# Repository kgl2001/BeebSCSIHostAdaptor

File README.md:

# BeebSCSIHostAdaptor
SCSI Host Adaptor that allows BBC &amp; Master Computers to interface with various SCSI Hard Disk Drives.

Please refer to the following discussion on Stardot for further details: https://stardot.org.uk/forums/viewtopic.php?f=3&t=18815

## Author

BeebSCSIHostAdaptor is developed and maintained by Ken Lowe.

The design is based on the BeebSCSI project by Simon Inns: https://github.com/simoninns/BeebSCSI

## Software License (GPLv3)

    BeebSCSI is free software: you can redistribute it and/or modify
    it under the terms of the GNU General Public License as published by
    the Free Software Foundation, either version 3 of the License, or
    (at your option) any later version.

    BeebSCSI is distributed in the hope that it will be useful,
    but WITHOUT ANY WARRANTY; without even the implied warranty of
    MERCHANTABILITY or FITNESS FOR A PARTICULAR PURPOSE.  See the
    GNU General Public License for more details.

    You should have received a copy of the GNU General Public License
    along with BeebSCSI.  If not, see <http://www.gnu.org/licenses/>.
    
## Hardware License (Creative Commons BY-SA 4.0)

Please see the following link for details: https://creativecommons.org/licenses/by-sa/4.0/

You are free to:

Share - copy and redistribute the material in any medium or format
Adapt - remix, transform, and build upon the material
for any purpose, even commercially.

This license is acceptable for Free Cultural Works.

The licensor cannot revoke these freedoms as long as you follow the license terms.

Under the following terms:

Attribution - You must give appropriate credit, provide a link to the license, and indicate if changes were made. You may do so in any reasonable manner, but not in any way that suggests the licensor endorses you or your use.

ShareAlike - If you remix, transform, or build upon the material, you must distribute your contributions under the same license as the original.

No additional restrictions - You may not apply legal terms or technological measures that legally restrict others from doing anything the license permits.

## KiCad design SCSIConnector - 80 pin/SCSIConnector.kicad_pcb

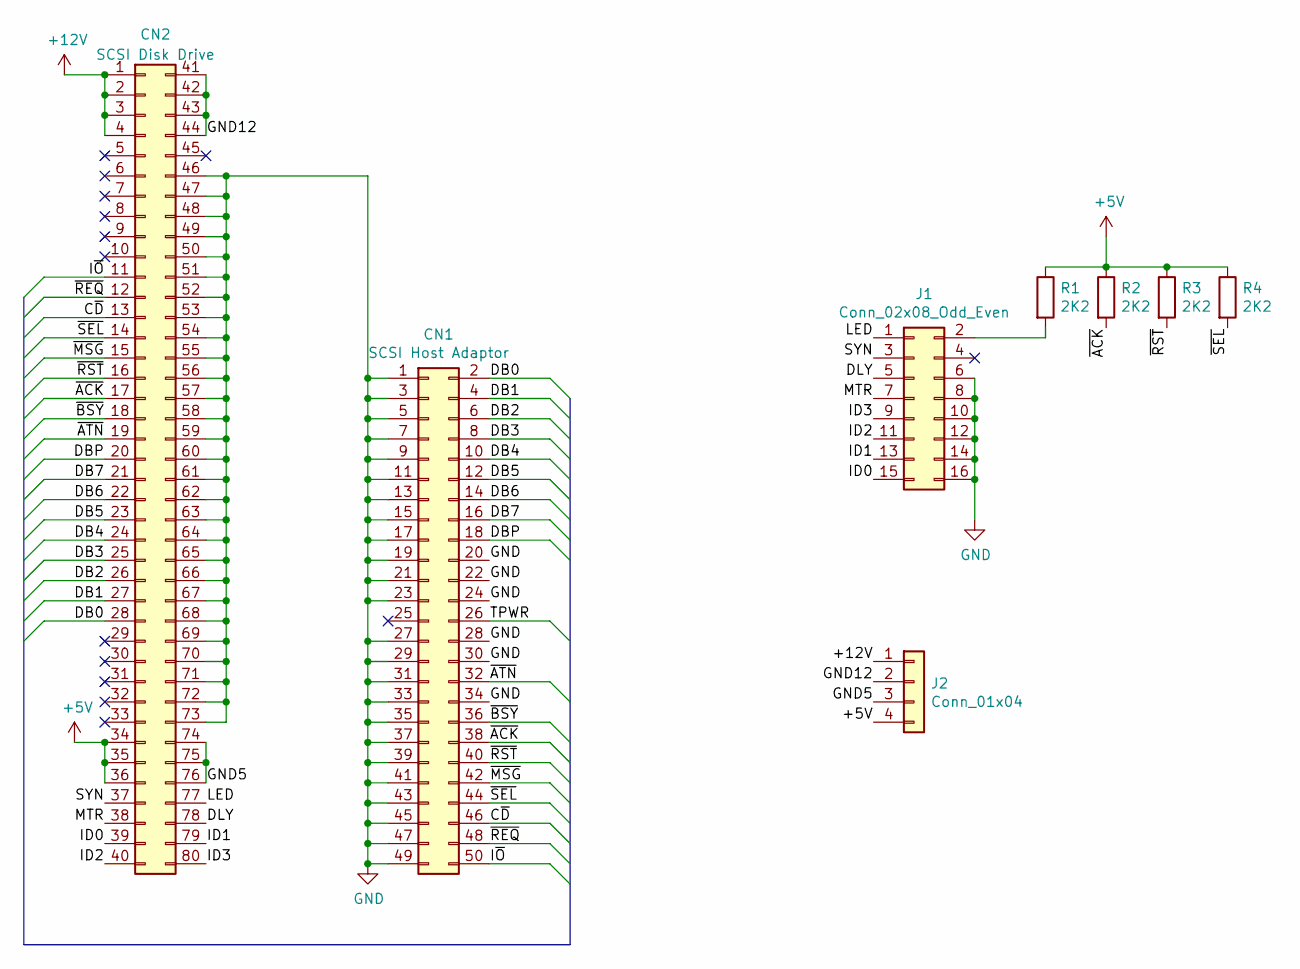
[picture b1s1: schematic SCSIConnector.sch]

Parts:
CN1: SCSI Host Adaptor; PinSocket_2x25_P2.54mm_Vertical
CN2: SCSI Disk Drive; TE_787311-4
J1: Conn_02x08_Odd_Even; PinHeader_2x08_P2.54mm_Vertical
J2: Conn_01x04; conn_hdd_15-24-4449
R1, R2, R3, R4: 2K2; R_Axial_DIN0204_L3.6mm_D1.6mm_P5.08mm_Horizontal

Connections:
+5V: CN2.34, CN2.35, CN2.36, J2.4, R1.1, R2.1, R3.1, R4.1
+12V: CN2.1, CN2.2, CN2.3, CN2.4, J2.1
/C~D: CN1.46, CN2.13
/DB0: CN1.2, CN2.28
/DB1: CN1.4, CN2.27
/DB2: CN1.6, CN2.26
/DB3: CN1.8, CN2.25
/DB4: CN1.10, CN2.24
/DB5: CN1.12, CN2.23
/DB6: CN1.14, CN2.22
/DB7: CN1.16, CN2.21
/DBP: CN1.18, CN2.20
/DLY: CN2.78, J1.5
/GND5: CN2.74, CN2.75, CN2.76, J2.3
/GND12: CN2.41, CN2.42, CN2.43, CN2.44, J2.2
/ID0: CN2.39, J1.15
/ID1: CN2.79, J1.13
/ID2: CN2.40, J1.11
/ID3: CN2.80, J1.9
/I~O: CN1.50, CN2.11
/LED: CN2.77, J1.1
/MTR: CN2.38, J1.7
/SYN: CN2.37, J1.3
/TPWR: CN1.26
/~ACK: CN1.38, CN2.17, R2.2
/~ATN: CN1.32, CN2.19
/~BSY: CN1.36, CN2.18
/~MSG: CN1.42, CN2.15
/~REQ: CN1.48, CN2.12
/~RST: CN1.40, CN2.16, R3.2
/~SEL: CN1.44, CN2.14, R4.2
GND: CN1.1, CN1.3, CN1.5, CN1.7, CN1.9, CN1.11, CN1.13, CN1.15, CN1.17, CN1.19, CN1.20, CN1.21, CN1.22, CN1.23, CN1.24, CN1.27, CN1.28, CN1.29, CN1.30, CN1.31, CN1.33, CN1.34, CN1.35, CN1.37, CN1.39, CN1.41, CN1.43, CN1.45, CN1.47, CN1.49, CN2.46, CN2.47, CN2.48, CN2.49, CN2.50, CN2.51, CN2.52, CN2.53, CN2.54, CN2.55, CN2.56, CN2.57, CN2.58, CN2.59, CN2.60, CN2.61, CN2.62, CN2.63, CN2.64, CN2.65, CN2.66, CN2.67, CN2.68, CN2.69, CN2.70, CN2.71, CN2.72, CN2.73, J1.6, J1.8, J1.10, J1.12, J1.14, J1.16
unnamed: J1.2, R1.2

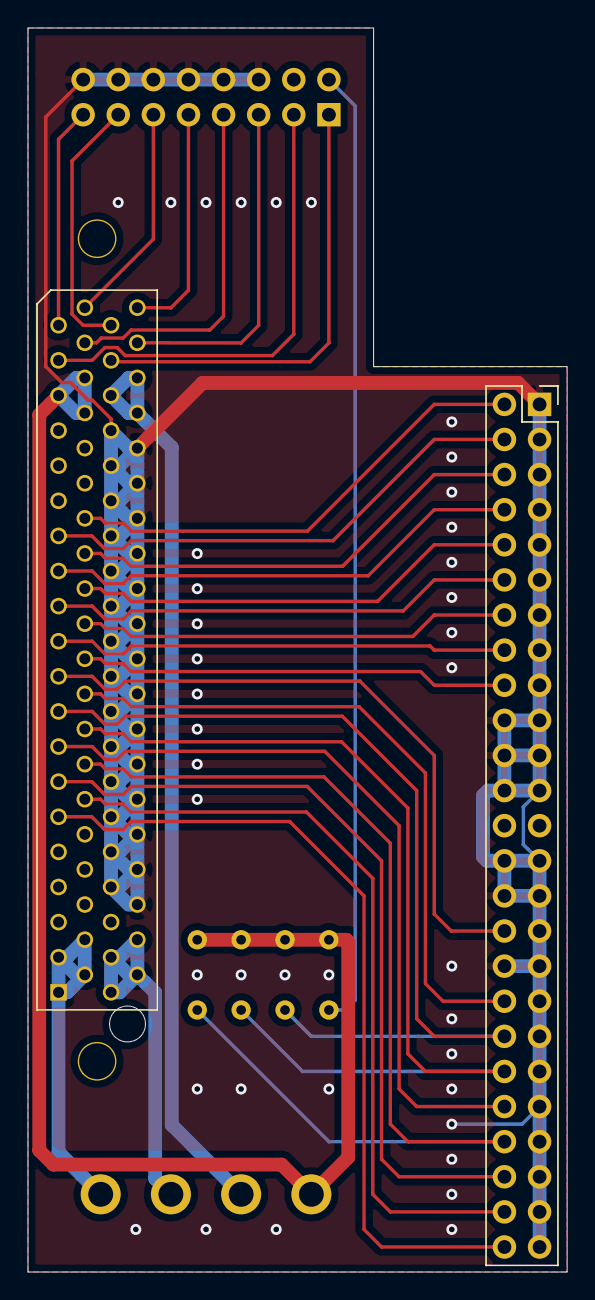
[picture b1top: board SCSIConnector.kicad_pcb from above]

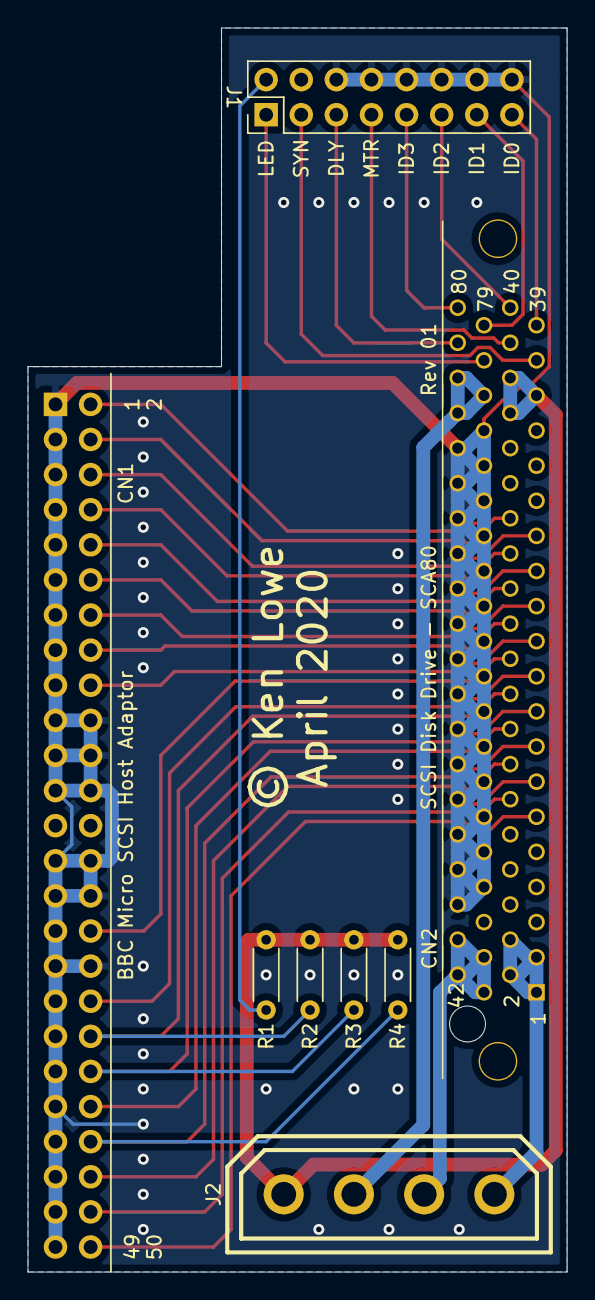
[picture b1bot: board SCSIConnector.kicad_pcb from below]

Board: 2 copper layers, 39.0 x 90.0 mm, 8 parts (6 on the bottom side), 32 nets.

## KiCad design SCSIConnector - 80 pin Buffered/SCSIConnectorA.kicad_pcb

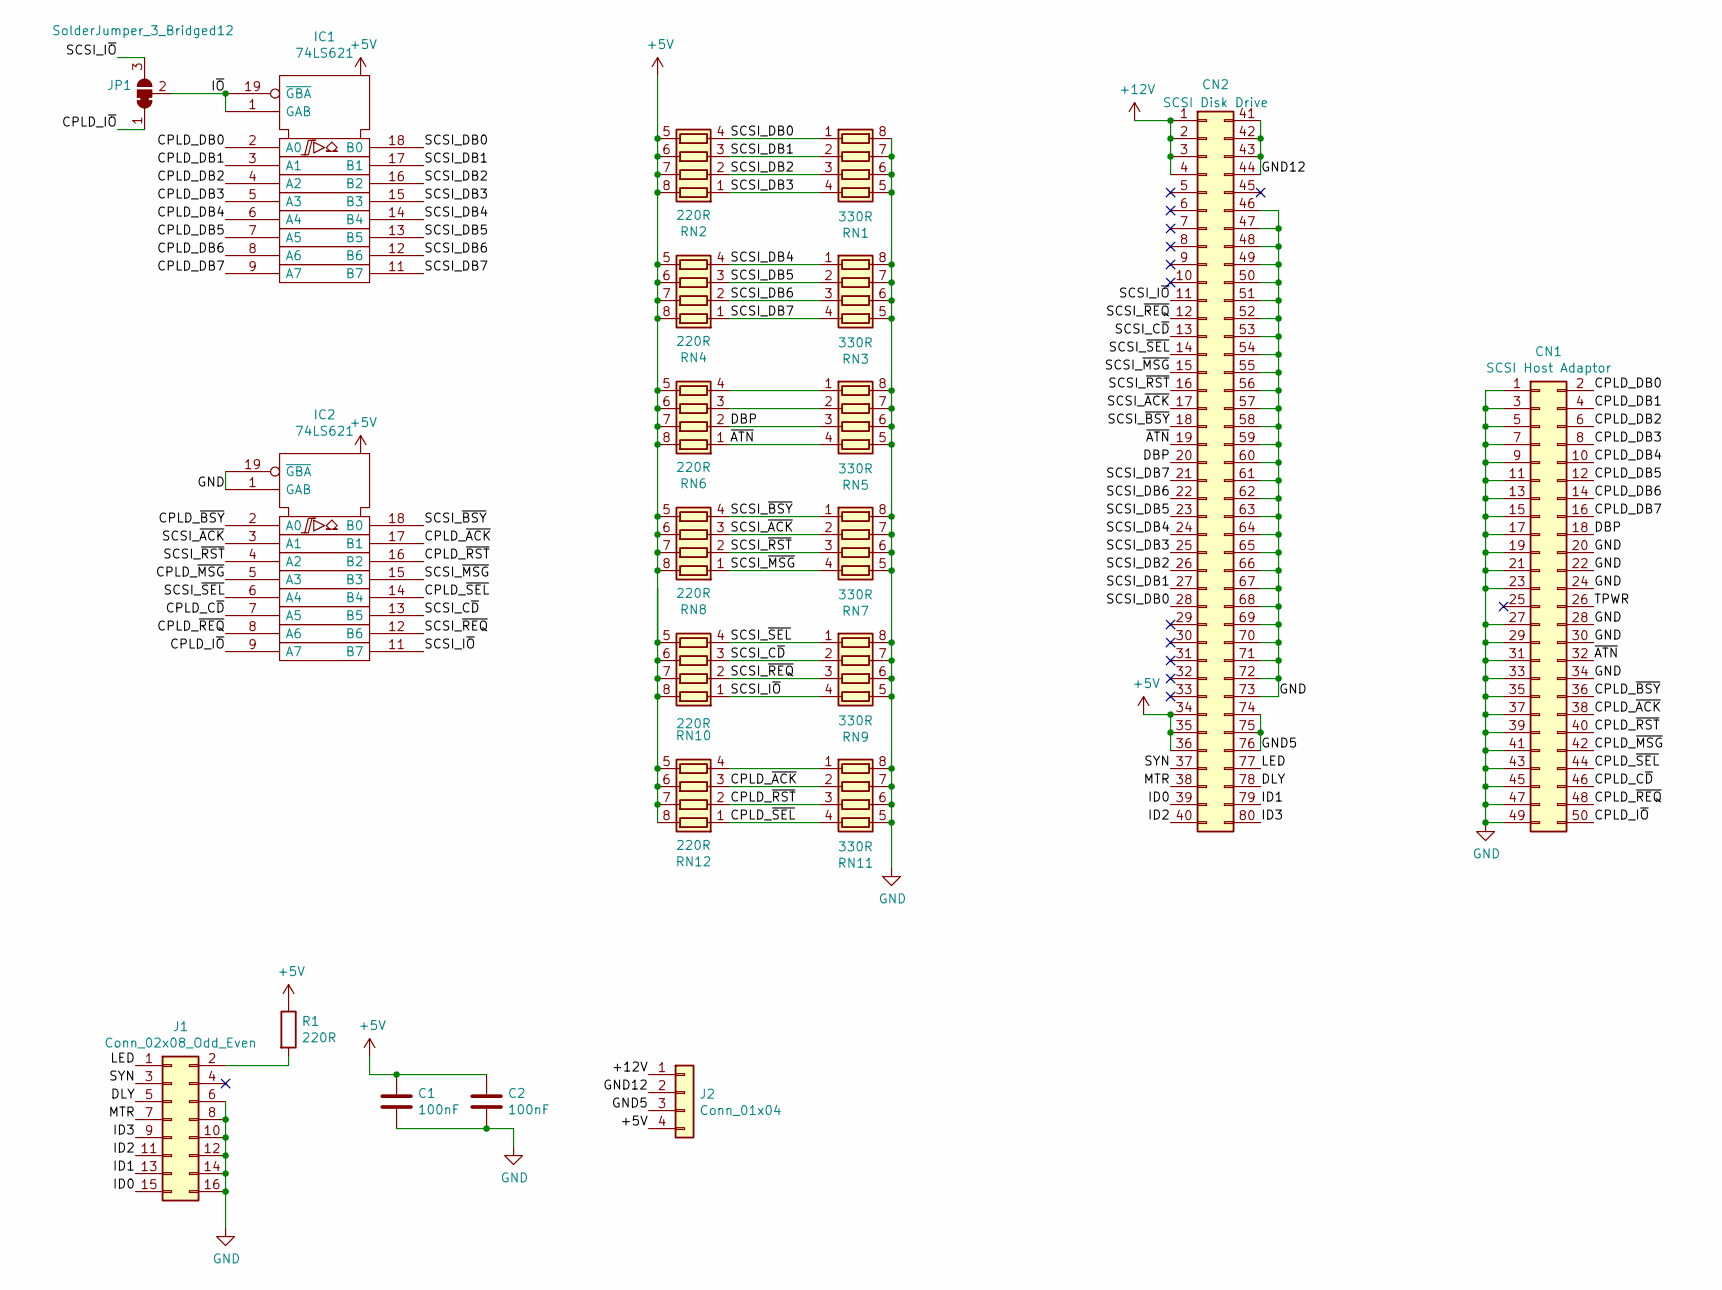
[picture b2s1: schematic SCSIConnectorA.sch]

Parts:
C1, C2: 100nF; C_0603_1608Metric
CN1: SCSI Host Adaptor; PinSocket_2x25_P2.54mm_Vertical
CN2: SCSI Disk Drive; TE_787311-4
IC1, IC2: 74LS621; SOIC-20W_7.5x12.8mm_P1.27mm
J1: Conn_02x08_Odd_Even; PinHeader_2x08_P2.54mm_Vertical
J2: Conn_01x04; conn_hdd_15-24-4449
JP1: SolderJumper_3_Bridged12; SolderJumper-3_P1.3mm_Bridged12_RoundedPad1.0x1.5mm
R1: 220R; R_0603_1608Metric
RN1, RN3, RN5, RN7, RN9, RN11: 330R; R_Array_Concave_4x0402
RN2, RN4, RN6, RN8, RN10, RN12: 220R; R_Array_Concave_4x0402

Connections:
+5V: C1.1, C2.1, CN2.34, CN2.35, CN2.36, IC1.20 (VCC), IC2.20 (VCC), J2.4, R1.1, RN2.5 (R4.2), RN2.6 (R3.2), RN2.7 (R2.2), RN2.8 (R1.2), RN4.5 (R4.2), RN4.6 (R3.2), RN4.7 (R2.2), RN4.8 (R1.2), RN6.5 (R4.2), RN6.6 (R3.2), RN6.7 (R2.2), RN6.8 (R1.2), RN8.5 (R4.2), RN8.6 (R3.2), RN8.7 (R2.2), RN8.8 (R1.2), RN10.5 (R4.2), RN10.6 (R3.2), RN10.7 (R2.2), RN10.8 (R1.2), RN12.5 (R4.2), RN12.6 (R3.2), RN12.7 (R2.2), RN12.8 (R1.2)
+12V: CN2.1, CN2.2, CN2.3, CN2.4, J2.1
/CPLD_C~D: CN1.46, IC2.7 (A5)
/CPLD_DB0: CN1.2, IC1.2 (A0)
/CPLD_DB1: CN1.4, IC1.3 (A1)
/CPLD_DB2: CN1.6, IC1.4 (A2)
/CPLD_DB3: CN1.8, IC1.5 (A3)
/CPLD_DB4: CN1.10, IC1.6 (A4)
/CPLD_DB5: CN1.12, IC1.7 (A5)
/CPLD_DB6: CN1.14, IC1.8 (A6)
/CPLD_DB7: CN1.16, IC1.9 (A7)
/CPLD_I~O: CN1.50, IC2.9 (A7), JP1.1 (A)
/CPLD_~ACK: CN1.38, IC2.17 (B1), RN11.2 (R2.1), RN12.3 (R3.1)
/CPLD_~BSY: CN1.36, IC2.2 (A0)
/CPLD_~MSG: CN1.42, IC2.5 (A3)
/CPLD_~REQ: CN1.48, IC2.8 (A6)
/CPLD_~RST: CN1.40, IC2.16 (B2), RN11.3 (R3.1), RN12.2 (R2.1)
/CPLD_~SEL: CN1.44, IC2.14 (B4), RN11.4 (R4.1), RN12.1 (R1.1)
/DBP: CN1.18, CN2.20, RN5.3 (R3.1), RN6.2 (R2.1)
/DLY: CN2.78, J1.5
/GND5: CN2.74, CN2.75, CN2.76, J2.3
/GND12: CN2.41, CN2.42, CN2.43, CN2.44, J2.2
/ID0: CN2.39, J1.15
/ID1: CN2.79, J1.13
/ID2: CN2.40, J1.11
/ID3: CN2.80, J1.9
/I~O: IC1.1 (GAB), IC1.19 (~GBA), JP1.2 (C)
/LED: CN2.77, J1.1
/MTR: CN2.38, J1.7
/SCSI_C~D: CN2.13, IC2.13 (B5), RN9.2 (R2.1), RN10.3 (R3.1)
/SCSI_DB0: CN2.28, IC1.18 (B0), RN1.1 (R1.1), RN2.4 (R4.1)
/SCSI_DB1: CN2.27, IC1.17 (B1), RN1.2 (R2.1), RN2.3 (R3.1)
/SCSI_DB2: CN2.26, IC1.16 (B2), RN1.3 (R3.1), RN2.2 (R2.1)
/SCSI_DB3: CN2.25, IC1.15 (B3), RN1.4 (R4.1), RN2.1 (R1.1)
/SCSI_DB4: CN2.24, IC1.14 (B4), RN3.1 (R1.1), RN4.4 (R4.1)
/SCSI_DB5: CN2.23, IC1.13 (B5), RN3.2 (R2.1), RN4.3 (R3.1)
/SCSI_DB6: CN2.22, IC1.12 (B6), RN3.3 (R3.1), RN4.2 (R2.1)
/SCSI_DB7: CN2.21, IC1.11 (B7), RN3.4 (R4.1), RN4.1 (R1.1)
/SCSI_I~O: CN2.11, IC2.11 (B7), JP1.3 (B), RN9.4 (R4.1), RN10.1 (R1.1)
/SCSI_~ACK: CN2.17, IC2.3 (A1), RN7.2 (R2.1), RN8.3 (R3.1)
/SCSI_~BSY: CN2.18, IC2.18 (B0), RN7.1 (R1.1), RN8.4 (R4.1)
/SCSI_~MSG: CN2.15, IC2.15 (B3), RN7.4 (R4.1), RN8.1 (R1.1)
/SCSI_~REQ: CN2.12, IC2.12 (B6), RN9.3 (R3.1), RN10.2 (R2.1)
/SCSI_~RST: CN2.16, IC2.4 (A2), RN7.3 (R3.1), RN8.2 (R2.1)
/SCSI_~SEL: CN2.14, IC2.6 (A4), RN9.1 (R1.1), RN10.4 (R4.1)
/SYN: CN2.37, J1.3
/TPWR: CN1.26
/~ATN: CN1.32, CN2.19, RN5.4 (R4.1), RN6.1 (R1.1)
GND: C1.2, C2.2, CN1.1, CN1.3, CN1.5, CN1.7, CN1.9, CN1.11, CN1.13, CN1.15, CN1.17, CN1.19, CN1.20, CN1.21, CN1.22, CN1.23, CN1.24, CN1.27, CN1.28, CN1.29, CN1.30, CN1.31, CN1.33, CN1.34, CN1.35, CN1.37, CN1.39, CN1.41, CN1.43, CN1.45, CN1.47, CN1.49, CN2.46, CN2.47, CN2.48, CN2.49, CN2.50, CN2.51, CN2.52, CN2.53, CN2.54, CN2.55, CN2.56, CN2.57, CN2.58, CN2.59, CN2.60, CN2.61, CN2.62, CN2.63, CN2.64, CN2.65, CN2.66, CN2.67, CN2.68, CN2.69, CN2.70, CN2.71, CN2.72, CN2.73, IC1.10 (GND), IC2.1 (GAB), IC2.10 (GND), IC2.19 (~GBA), J1.6, J1.8, J1.10, J1.12, J1.14, J1.16, RN1.5 (R4.2), RN1.6 (R3.2), RN1.7 (R2.2), RN1.8 (R1.2), RN3.5 (R4.2), RN3.6 (R3.2), RN3.7 (R2.2), RN3.8 (R1.2), RN5.5 (R4.2), RN5.6 (R3.2), RN5.7 (R2.2), RN5.8 (R1.2), RN7.5 (R4.2), RN7.6 (R3.2), RN7.7 (R2.2), RN7.8 (R1.2), RN9.5 (R4.2), RN9.6 (R3.2), RN9.7 (R2.2), RN9.8 (R1.2), RN11.5 (R4.2), RN11.6 (R3.2), RN11.7 (R2.2), RN11.8 (R1.2)
unnamed: J1.2, R1.2
unnamed: RN5.1 (R1.1), RN6.4 (R4.1)
unnamed: RN5.2 (R2.1), RN6.3 (R3.1)
unnamed: RN11.1 (R1.1), RN12.4 (R4.1)

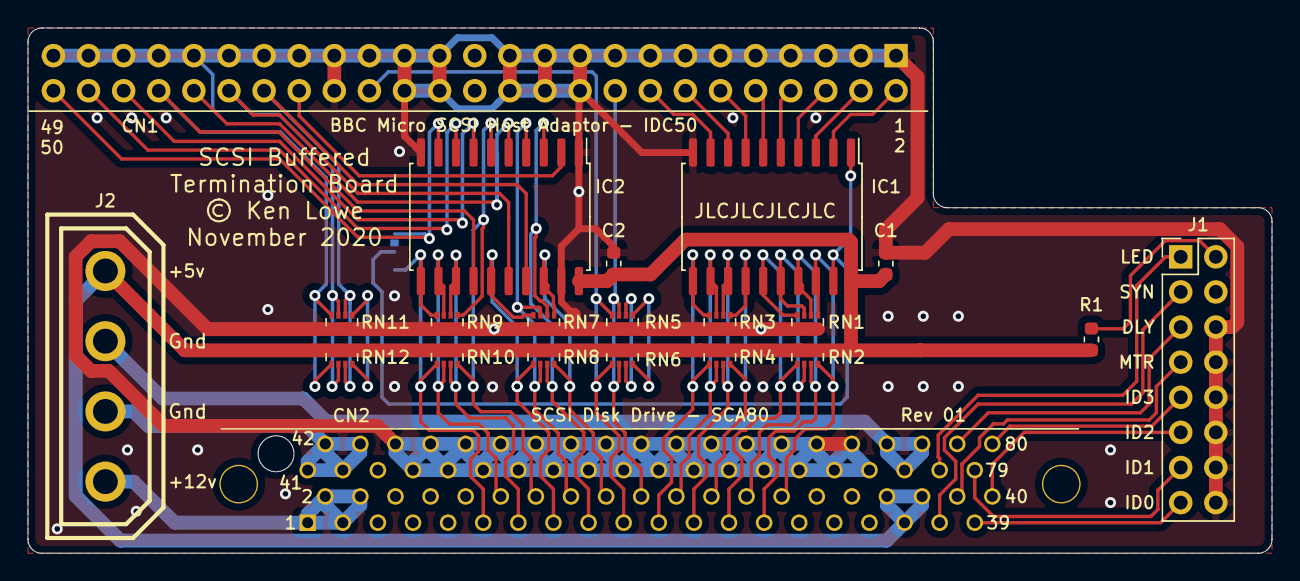
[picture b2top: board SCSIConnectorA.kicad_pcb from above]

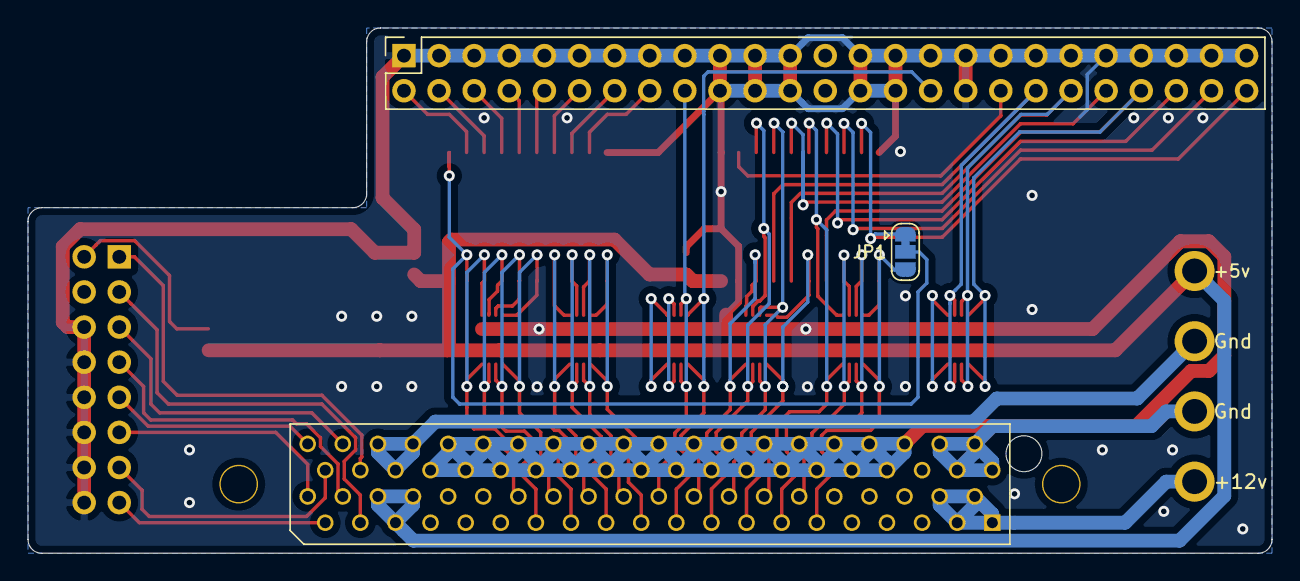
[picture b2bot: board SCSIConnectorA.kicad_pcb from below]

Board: 2 copper layers, 90.0 x 38.0 mm, 22 parts (3 on the bottom side), 52 nets.

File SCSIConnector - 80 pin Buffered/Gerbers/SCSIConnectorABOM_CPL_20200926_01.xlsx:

Designator | LCSC Part # | Footprint | JLCValue | Mid X | Mid Y | Rot | Side | Val | Package
C1 | C14663 | 0603 | 100nF | 156.83000000000001 | -74.819999999999993 | 90 | top | 100uF | C_0603_1608Metric
C2 | C14663 | 0603 | 100nF | 137.14500000000001 | -74.819999999999993 | 90 | top | 100uF | C_0603_1608Metric
IC1 |  |  |  | 148.595 | -71.435000000000002 | 270 | top | 74LS621 | SOIC-20W_7.5x12.8mm_P1.27mm
IC2 |  |  |  | 128.91 | -71.435000000000002 | 270 | top | 74LS621 | SOIC-20W_7.5x12.8mm_P1.27mm
R1 | C22962 | 0603 | 220R | 171.70424 | -80.305080000000004 | 90 | top | 220R | R_0603_1608Metric
RN1 | C102635 | 0402_x4 | 330R | 151.17500000000001 | -79.055000000000007 | 270 | top | 330R | R_Array_Concave_4x0402
RN2 | C25498 | 0402_x4 | 220R | 151.17500000000001 | -81.594999999999999 | 90 | top | 220R | R_Array_Concave_4x0402
RN3 | C102635 | 0402_x4 | 330R | 144.82499999999999 | -79.055000000000007 | 270 | top | 330R | R_Array_Concave_4x0402
RN4 | C25498 | 0402_x4 | 220R | 144.82499999999999 | -81.594999999999999 | 90 | top | 220R | R_Array_Concave_4x0402
RN5 | C102635 | 0402_x4 | 330R | 137.78 | -79.055000000000007 | 270 | top | 330R | R_Array_Concave_4x0402
RN6 | C25498 | 0402_x4 | 220R | 137.78 | -81.594999999999999 | 90 | top | 220R | R_Array_Concave_4x0402
RN7 | C102635 | 0402_x4 | 330R | 132.08500000000001 | -79.055000000000007 | 270 | top | 330R | R_Array_Concave_4x0402
RN8 | C25498 | 0402_x4 | 220R | 132.08500000000001 | -81.594999999999999 | 90 | top | 220R | R_Array_Concave_4x0402
RN9 | C102635 | 0402_x4 | 330R | 125.1 | -79.055000000000007 | 270 | top | 330R | R_Array_Concave_4x0402
RN10 | C25498 | 0402_x4 | 220R | 125.1 | -81.594999999999999 | 90 | top | 220R | R_Array_Concave_4x0402
RN11 | C102635 | 0402_x4 | 330R | 117.48 | -79.055000000000007 | 270 | top | 330R | R_Array_Concave_4x0402
RN12 | C25498 | 0402_x4 | 220R | 117.48 | -81.594999999999999 | 90 | top | 220R | R_Array_Concave_4x0402

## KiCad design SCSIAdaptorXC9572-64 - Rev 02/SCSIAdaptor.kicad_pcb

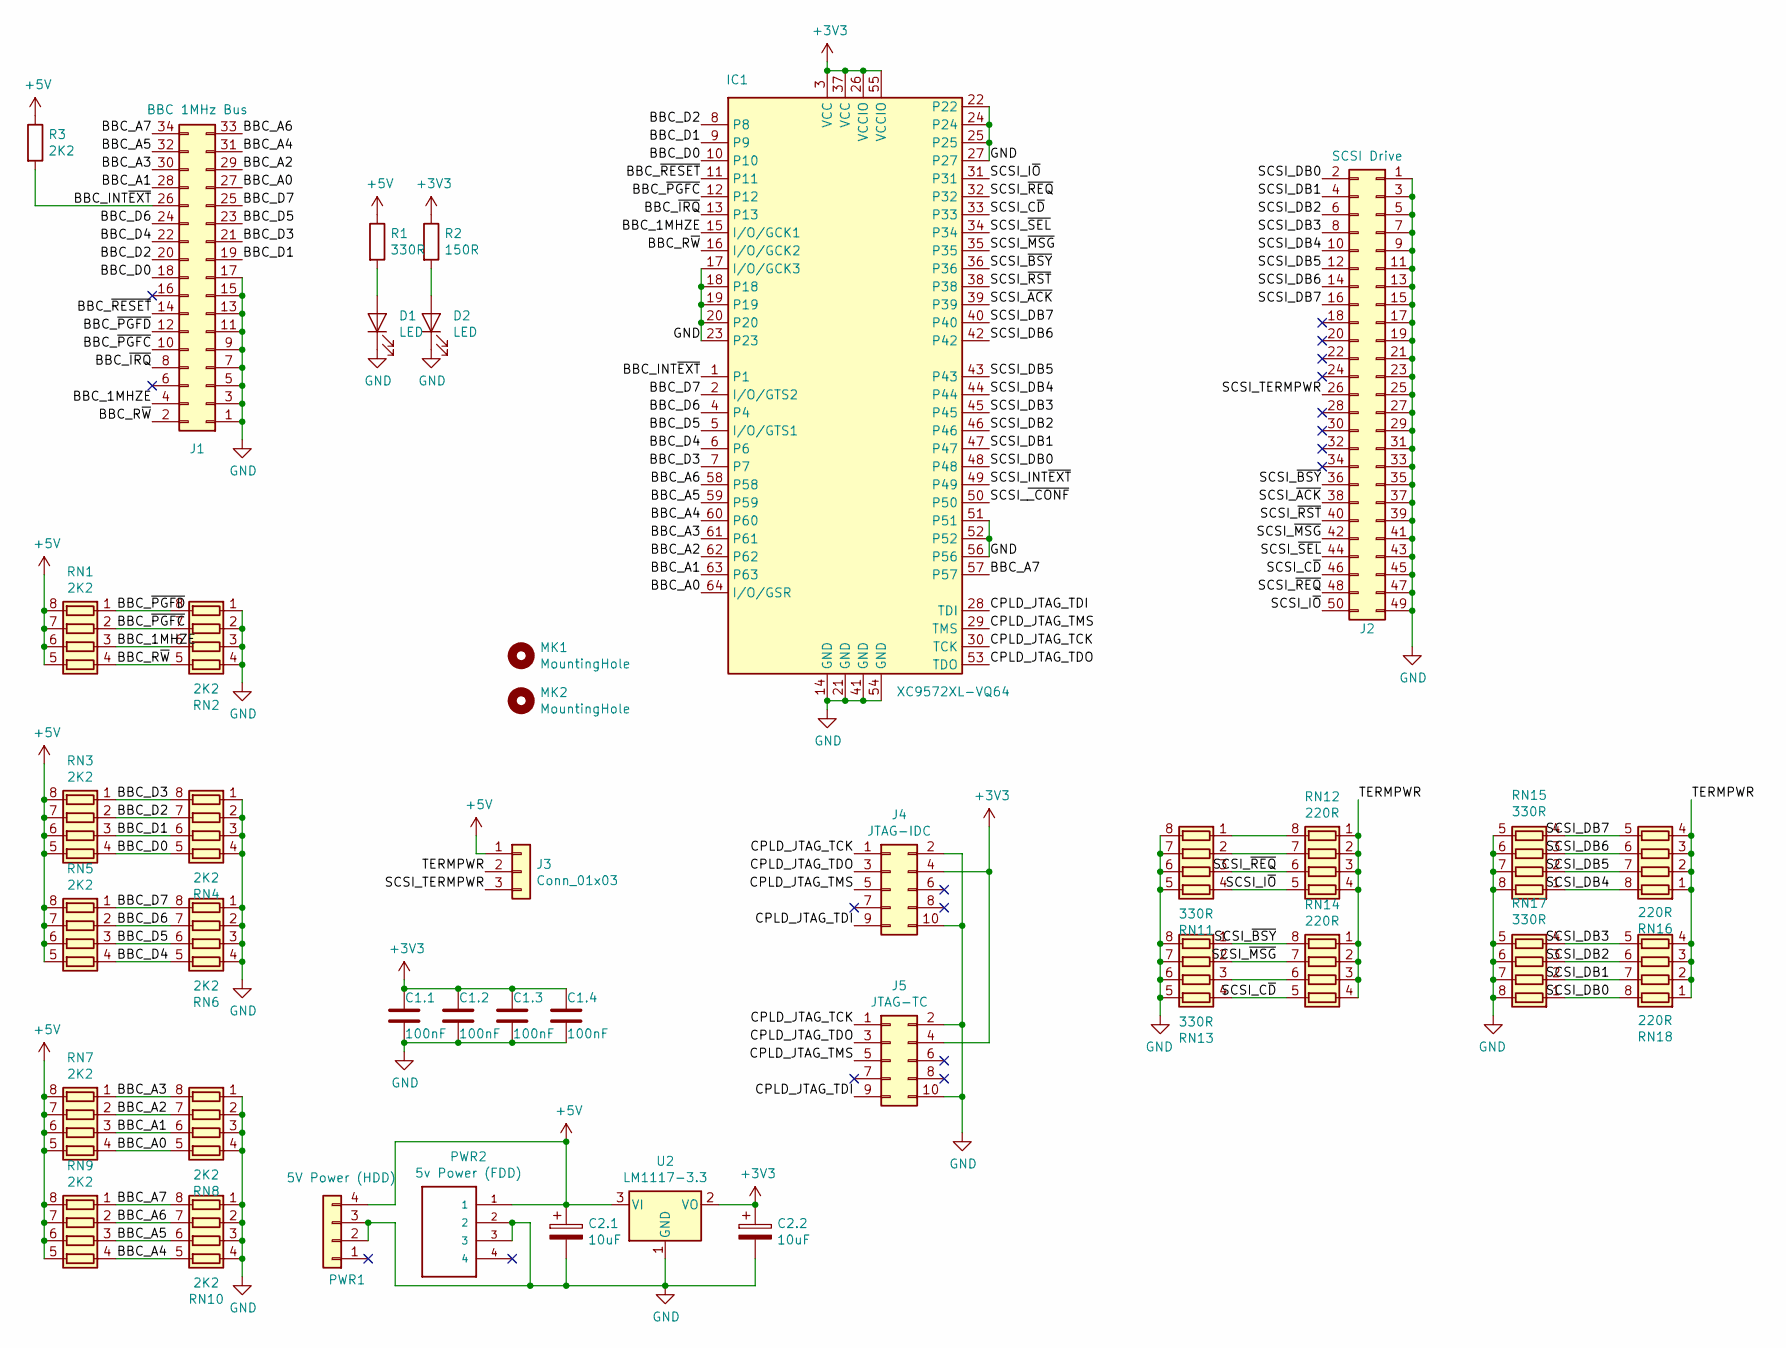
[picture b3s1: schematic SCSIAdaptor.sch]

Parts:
C1.1, C1.2, C1.3, C1.4: 100nF; C_0805_2012Metric
C2.1, C2.2: 10uF; C_1206_3216Metric
D1, D2: LED; LED_0603_1608Metric
IC1: XC9572XL-VQ64; TQFP-64_10x10mm_P0.5mm
J1: BBC 1MHz Bus; IDC-Header_2x17_P2.54mm_Horizontal
J2: SCSI Drive; IDC-Header_2x25_P2.54mm_Horizontal
J3: Conn_01x03; SolderJumper-3_P1.3mm_Bridged12_RoundedPad1.0x1.5mm
J4: JTAG-IDC; PinHeader_2x05_P2.54mm_Vertical
J5: JTAG-TC; Tag-Connect_TC2050-IDC-NL_2x05_P1.27mm_Vertical
MK1, MK2: MountingHole; MountingHole_3.2mm_M3
PWR1: 5V Power (HDD); conn_hdd_15-24-4441
PWR2: 5v Power (FDD); TE_171826-4
R1: 330R; R_0402_1005Metric
R2: 150R; R_0402_1005Metric
R3: 2K2; R_0402_1005Metric
RN1, RN2, RN3, RN4, RN5, RN6, RN7, RN8, RN9, RN10: 2K2; R_Array_Concave_4x0402
RN11, RN13, RN15, RN17: 330R; R_Array_Concave_4x0402
RN12, RN14, RN16, RN18: 220R; R_Array_Concave_4x0402
U2: LM1117-3.3; SOT-223-3_TabPin2

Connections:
+3V3: C1.1.1, C1.2.1, C1.3.1, C1.4.1, C2.2.1, IC1.3 (VCC), IC1.26 (VCCIO), IC1.37 (VCC), IC1.55 (VCCIO), J4.4, J5.4, R2.1, U2.2 (VO)
+5V: C2.1.1, J3.1, PWR1.4, PWR2.1, R1.1, R3.1, RN1.5 (R4.2), RN1.6 (R3.2), RN1.7 (R2.2), RN1.8 (R1.2), RN3.5 (R4.2), RN3.6 (R3.2), RN3.7 (R2.2), RN3.8 (R1.2), RN5.5 (R4.2), RN5.6 (R3.2), RN5.7 (R2.2), RN5.8 (R1.2), RN7.5 (R4.2), RN7.6 (R3.2), RN7.7 (R2.2), RN7.8 (R1.2), RN9.5 (R4.2), RN9.6 (R3.2), RN9.7 (R2.2), RN9.8 (R1.2), U2.3 (VI)
/BBC_1MHZE: IC1.15 (I/O/GCK1), J1.4, RN1.3 (R3.1), RN2.6 (R3.2)
/BBC_A0: IC1.64 (I/O/GSR), J1.27, RN7.4 (R4.1), RN8.5 (R4.2)
/BBC_A1: IC1.63, J1.28, RN7.3 (R3.1), RN8.6 (R3.2)
/BBC_A2: IC1.62, J1.29, RN7.2 (R2.1), RN8.7 (R2.2)
/BBC_A3: IC1.61, J1.30, RN7.1 (R1.1), RN8.8 (R1.2)
/BBC_A4: IC1.60, J1.31, RN9.4 (R4.1), RN10.5 (R4.2)
/BBC_A5: IC1.59, J1.32, RN9.3 (R3.1), RN10.6 (R3.2)
/BBC_A6: IC1.58, J1.33, RN9.2 (R2.1), RN10.7 (R2.2)
/BBC_A7: IC1.57, J1.34, RN9.1 (R1.1), RN10.8 (R1.2)
/BBC_D0: IC1.10, J1.18, RN3.4 (R4.1), RN4.5 (R4.2)
/BBC_D1: IC1.9, J1.19, RN3.3 (R3.1), RN4.6 (R3.2)
/BBC_D2: IC1.8, J1.20, RN3.2 (R2.1), RN4.7 (R2.2)
/BBC_D3: IC1.7, J1.21, RN3.1 (R1.1), RN4.8 (R1.2)
/BBC_D4: IC1.6, J1.22, RN5.4 (R4.1), RN6.5 (R4.2)
/BBC_D5: IC1.5 (I/O/GTS1), J1.23, RN5.3 (R3.1), RN6.6 (R3.2)
/BBC_D6: IC1.4, J1.24, RN5.2 (R2.1), RN6.7 (R2.2)
/BBC_D7: IC1.2 (I/O/GTS2), J1.25, RN5.1 (R1.1), RN6.8 (R1.2)
/BBC_INT~EXT: IC1.1, J1.26, R3.2
/BBC_R~W: IC1.16 (I/O/GCK2), J1.2, RN1.4 (R4.1), RN2.5 (R4.2)
/BBC_~IRQ: IC1.13, J1.8
/BBC_~PGFC: IC1.12, J1.10, RN1.2 (R2.1), RN2.7 (R2.2)
/BBC_~PGFD: J1.12, RN1.1 (R1.1), RN2.8 (R1.2)
/BBC_~RESET: IC1.11, J1.14
/CPLD_JTAG_TCK: IC1.30 (TCK), J4.1, J5.1
/CPLD_JTAG_TDI: IC1.28 (TDI), J4.9, J5.9
/CPLD_JTAG_TDO: IC1.53 (TDO), J4.3, J5.3
/CPLD_JTAG_TMS: IC1.29 (TMS), J4.5, J5.5
/SCSI_C~D: IC1.33, J2.46, RN13.4 (R4.1), RN14.5 (R4.2)
/SCSI_DB0: IC1.48, J2.2, RN17.1 (R1.1), RN18.8 (R1.2)
/SCSI_DB1: IC1.47, J2.4, RN17.2 (R2.1), RN18.7 (R2.2)
/SCSI_DB2: IC1.46, J2.6, RN17.3 (R3.1), RN18.6 (R3.2)
/SCSI_DB3: IC1.45, J2.8, RN17.4 (R4.1), RN18.5 (R4.2)
/SCSI_DB4: IC1.44, J2.10, RN15.1 (R1.1), RN16.8 (R1.2)
/SCSI_DB5: IC1.43, J2.12, RN15.2 (R2.1), RN16.7 (R2.2)
/SCSI_DB6: IC1.42, J2.14, RN15.3 (R3.1), RN16.6 (R3.2)
/SCSI_DB7: IC1.40, J2.16, RN15.4 (R4.1), RN16.5 (R4.2)
/SCSI_INT~EXT: IC1.49
/SCSI_I~O: IC1.31, J2.50, RN11.4 (R4.1), RN12.5 (R4.2)
/SCSI_TERMPWR: J2.26, J3.3
/SCSI_~ACK: IC1.39, J2.38
/SCSI_~BSY: IC1.36, J2.36, RN13.1 (R1.1), RN14.8 (R1.2)
/SCSI_~MSG: IC1.35, J2.42, RN13.2 (R2.1), RN14.7 (R2.2)
/SCSI_~REQ: IC1.32, J2.48, RN11.3 (R3.1), RN12.6 (R3.2)
/SCSI_~RST: IC1.38, J2.40
/SCSI_~SEL: IC1.34, J2.44
/SCSI_~_CONF: IC1.50
/TERMPWR: J3.2, RN12.1 (R1.1), RN12.2 (R2.1), RN12.3 (R3.1), RN12.4 (R4.1), RN14.1 (R1.1), RN14.2 (R2.1), RN14.3 (R3.1), RN14.4 (R4.1), RN16.1 (R1.1), RN16.2 (R2.1), RN16.3 (R3.1), RN16.4 (R4.1), RN18.1 (R1.1), RN18.2 (R2.1), RN18.3 (R3.1), RN18.4 (R4.1)
GND: C1.1.2, C1.2.2, C1.3.2, C1.4.2, C2.1.2, C2.2.2, D1.1 (K), D2.1 (K), IC1.14 (GND), IC1.17 (I/O/GCK3), IC1.18, IC1.19, IC1.20, IC1.21 (GND), IC1.22, IC1.23, IC1.24, IC1.25, IC1.27, IC1.41 (GND), IC1.51, IC1.52, IC1.54 (GND), IC1.56, J1.1, J1.3, J1.5, J1.7, J1.9, J1.11, J1.13, J1.15, J1.17, J2.1, J2.3, J2.5, J2.7, J2.9, J2.11, J2.13, J2.15, J2.17, J2.19, J2.21, J2.23, J2.25, J2.27, J2.29, J2.31, J2.33, J2.35, J2.37, J2.39, J2.41, J2.43, J2.45, J2.47, J2.49, J4.2, J4.10, J5.2, J5.10, PWR1.2, PWR1.3, PWR2.2, PWR2.3, RN2.1 (R1.1), RN2.2 (R2.1), RN2.3 (R3.1), RN2.4 (R4.1), RN4.1 (R1.1), RN4.2 (R2.1), RN4.3 (R3.1), RN4.4 (R4.1), RN6.1 (R1.1), RN6.2 (R2.1), RN6.3 (R3.1), RN6.4 (R4.1), RN8.1 (R1.1), RN8.2 (R2.1), RN8.3 (R3.1), RN8.4 (R4.1), RN10.1 (R1.1), RN10.2 (R2.1), RN10.3 (R3.1), RN10.4 (R4.1), RN11.5 (R4.2), RN11.6 (R3.2), RN11.7 (R2.2), RN11.8 (R1.2), RN13.5 (R4.2), RN13.6 (R3.2), RN13.7 (R2.2), RN13.8 (R1.2), RN15.5 (R4.2), RN15.6 (R3.2), RN15.7 (R2.2), RN15.8 (R1.2), RN17.5 (R4.2), RN17.6 (R3.2), RN17.7 (R2.2), RN17.8 (R1.2), U2.1 (GND)
unnamed: D1.2 (A), R1.2
unnamed: D2.2 (A), R2.2
unnamed: RN11.1 (R1.1), RN12.8 (R1.2)
unnamed: RN11.2 (R2.1), RN12.7 (R2.2)
unnamed: RN13.3 (R3.1), RN14.6 (R3.2)

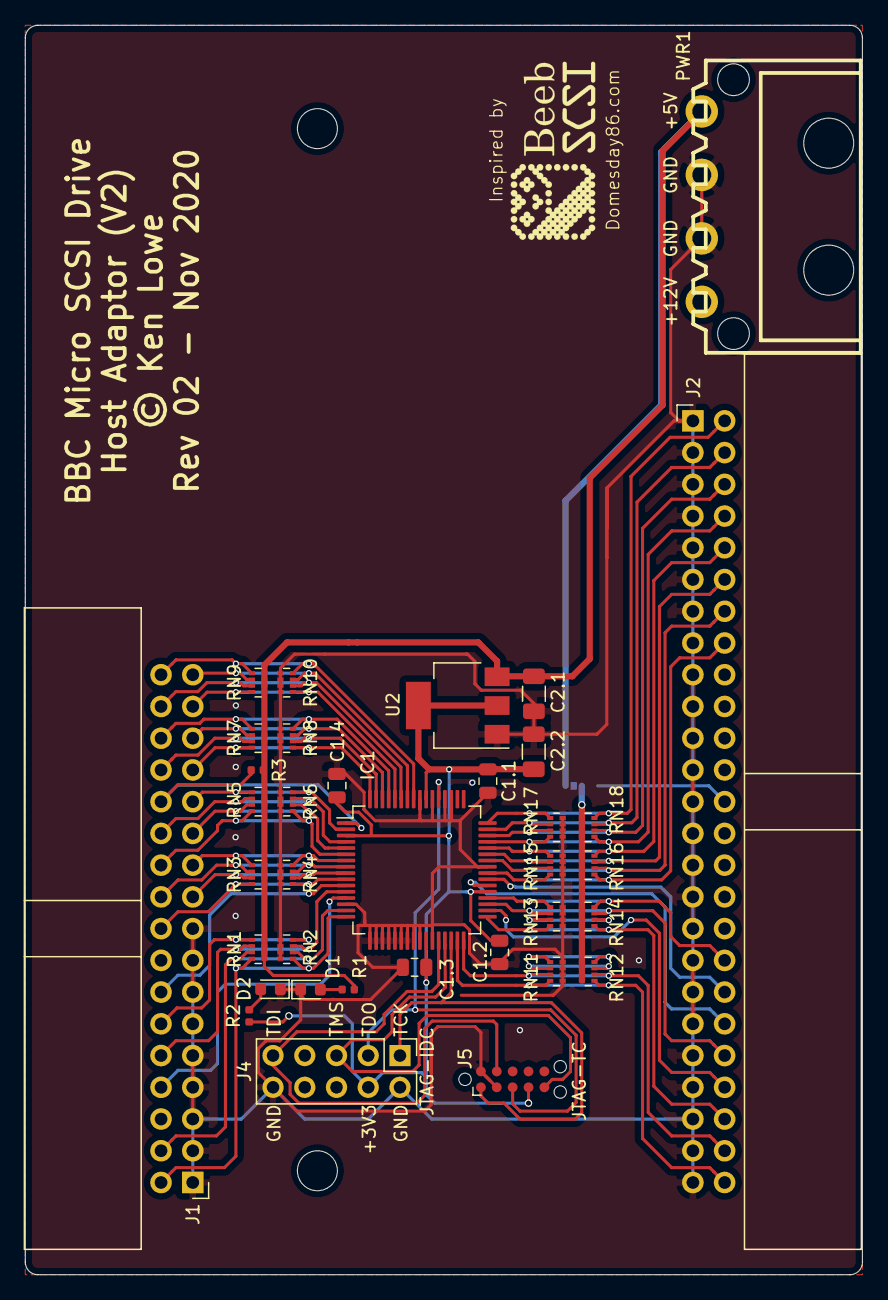
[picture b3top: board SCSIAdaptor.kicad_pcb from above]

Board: 2 copper layers, 67.0 x 100.0 mm, 39 parts (1 on the bottom side), 53 nets.

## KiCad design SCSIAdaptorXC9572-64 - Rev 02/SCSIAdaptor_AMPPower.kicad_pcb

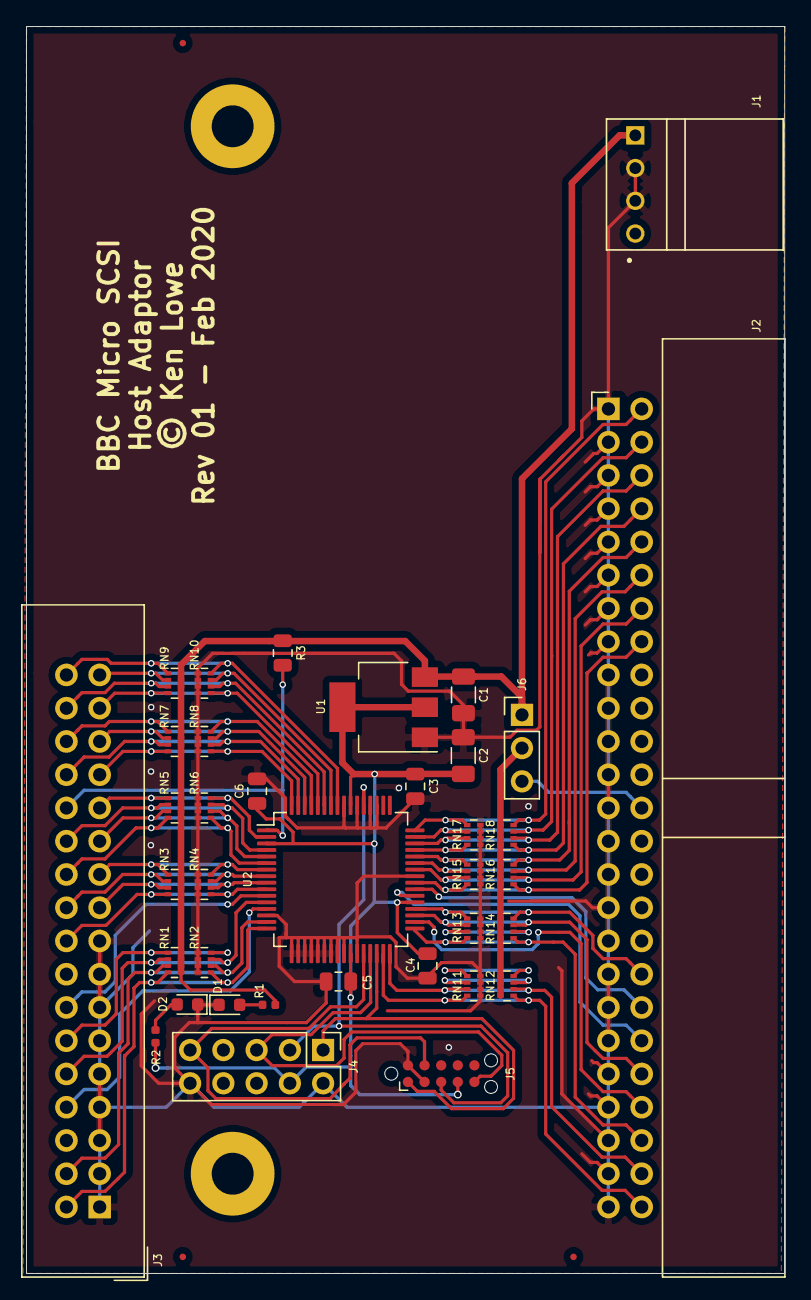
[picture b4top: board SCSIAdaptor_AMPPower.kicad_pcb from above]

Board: 2 copper layers, 57.9 x 95.2 mm, 42 parts (0 on the bottom side), 53 nets.

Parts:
C1, C2: 10uF; C_1206_3216Metric
C3, C4, C5, C6: 100nF; C_0805_2012Metric
D1, D2: LED; LED_0603_1608Metric
F1, F2, F3: Fiducial; Fiducial_0.5mm_Dia_1mm_Outer
J1: 5v Power (FDD); TE_171826-4
J2: SCSI Drive; IDC-Header_2x25_P2.54mm_Horizontal
J3: BBC 1MHz Bus; IDC-Header_2x17_P2.54mm_Vertical
J4: JTAG-IDC; PinHeader_2x05_P2.54mm_Vertical
J5: JTAG-TC; Tag-Connect_TC2050-IDC-NL_2x05_P1.27mm_Vertical
J6: Conn_01x03; PinHeader_1x03_P2.54mm_Vertical
MK1, MK2: MountingHole; MountingHole_3.2mm_M3_Pad
R1: 330R; R_0402_1005Metric
R2: 150R; R_0402_1005Metric
R3: 2K2; R_0805_2012Metric
RN1, RN2, RN3, RN4, RN5, RN6, RN7, RN8, RN9, RN10: 2K2; R_Array_Concave_4x0402
RN11, RN13, RN15, RN17: 330R; R_Array_Concave_4x0402
RN12, RN14, RN16, RN18: 220R; R_Array_Concave_4x0402
U1: LM1117-3.3; SOT-223-3_TabPin2
U2: XC9572XL-VQ64; TQFP-64_10x10mm_P0.5mm

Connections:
+3V3: C2.1, C3.1, C4.1, C5.1, C6.1, J4.4, J5.4, R2.1, U1.2, U2.3, U2.26, U2.37, U2.55
+5V: C1.1, J1.1, J6.1, R1.1, R3.1, RN1.5, RN1.6, RN1.7, RN1.8, RN3.5, RN3.6, RN3.7, RN3.8, RN5.5, RN5.6, RN5.7, RN5.8, RN7.5, RN7.6, RN7.7, RN7.8, RN9.5, RN9.6, RN9.7, RN9.8, U1.3
/BBC_1MHZE: J3.4, RN1.3, RN2.6, U2.15
/BBC_A0: J3.27, RN7.4, RN8.5, U2.64
/BBC_A1: J3.28, RN7.3, RN8.6, U2.63
/BBC_A2: J3.29, RN7.2, RN8.7, U2.62
/BBC_A3: J3.30, RN7.1, RN8.8, U2.61
/BBC_A4: J3.31, RN9.4, RN10.5, U2.60
/BBC_A5: J3.32, RN9.3, RN10.6, U2.59
/BBC_A6: J3.33, RN9.2, RN10.7, U2.58
/BBC_A7: J3.34, RN9.1, RN10.8, U2.57
/BBC_D0: J3.18, RN3.4, RN4.5, U2.10
/BBC_D1: J3.19, RN3.3, RN4.6, U2.9
/BBC_D2: J3.20, RN3.2, RN4.7, U2.8
/BBC_D3: J3.21, RN3.1, RN4.8, U2.7
/BBC_D4: J3.22, RN5.4, RN6.5, U2.6
/BBC_D5: J3.23, RN5.3, RN6.6, U2.5
/BBC_D6: J3.24, RN5.2, RN6.7, U2.4
/BBC_D7: J3.25, RN5.1, RN6.8, U2.2
/BBC_INT~EXT: J3.26, R3.2, U2.1
/BBC_R~W: J3.2, RN1.4, RN2.5, U2.16
/BBC_~IRQ: J3.8, U2.13
/BBC_~PGFC: J3.10, RN1.2, RN2.7, U2.12
/BBC_~PGFD: J3.12, RN1.1, RN2.8
/BBC_~RESET: J3.14, U2.11
/CPLD_JTAG_TCK: J4.1, J5.1, U2.30
/CPLD_JTAG_TDI: J4.9, J5.9, U2.28
/CPLD_JTAG_TDO: J4.3, J5.3, U2.53
/CPLD_JTAG_TMS: J4.5, J5.5, U2.29
/SCSI_C~D: J2.46, RN13.4, RN14.5, U2.33
/SCSI_DB0: J2.2, RN17.1, RN18.8, U2.48
/SCSI_DB1: J2.4, RN17.2, RN18.7, U2.47
/SCSI_DB2: J2.6, RN17.3, RN18.6, U2.46
/SCSI_DB3: J2.8, RN17.4, RN18.5, U2.45
/SCSI_DB4: J2.10, RN15.1, RN16.8, U2.44
/SCSI_DB5: J2.12, RN15.2, RN16.7, U2.43
/SCSI_DB6: J2.14, RN15.3, RN16.6, U2.42
/SCSI_DB7: J2.16, RN15.4, RN16.5, U2.40
/SCSI_I~O: J2.50, RN11.4, RN12.5, U2.31
/SCSI_TERMPWR: J2.26, J6.3
/SCSI_~ACK: J2.38, U2.39
/SCSI_~BSY: J2.36, RN13.1, RN14.8, U2.36
/SCSI_~MSG: J2.42, RN13.2, RN14.7, U2.35
/SCSI_~REQ: J2.48, RN11.3, RN12.6, U2.32
/SCSI_~RST: J2.40, U2.38
/SCSI_~SEL: J2.44, U2.34
/TERMPWR: J6.2, RN12.1, RN12.2, RN12.3, RN12.4, RN14.1, RN14.2, RN14.3, RN14.4, RN16.1, RN16.2, RN16.3, RN16.4, RN18.1, RN18.2, RN18.3, RN18.4
GND: C1.2, C2.2, C3.2, C4.2, C5.2, C6.2, D1.1, D2.1, J1.2, J1.3, J2.1, J2.3, J2.5, J2.7, J2.9, J2.11, J2.13, J2.15, J2.17, J2.19, J2.21, J2.23, J2.25, J2.27, J2.29, J2.31, J2.33, J2.35, J2.37, J2.39, J2.41, J2.43, J2.45, J2.47, J2.49, J3.1, J3.3, J3.5, J3.7, J3.9, J3.11, J3.13, J3.15, J3.17, J4.2, J4.10, J5.2, J5.10, RN2.1, RN2.2, RN2.3, RN2.4, RN4.1, RN4.2, RN4.3, RN4.4, RN6.1, RN6.2, RN6.3, RN6.4, RN8.1, RN8.2, RN8.3, RN8.4, RN10.1, RN10.2, RN10.3, RN10.4, RN11.5, RN11.6, RN11.7, RN11.8, RN13.5, RN13.6, RN13.7, RN13.8, RN15.5, RN15.6, RN15.7, RN15.8, RN17.5, RN17.6, RN17.7, RN17.8, U1.1, U2.14, U2.17, U2.18, U2.19, U2.20, U2.21, U2.22, U2.23, U2.24, U2.25, U2.27, U2.41, U2.51, U2.52, U2.54, U2.56
unnamed: D1.2, R1.2
unnamed: D2.2, R2.2
unnamed: RN11.1, RN12.8
unnamed: RN11.2, RN12.7
unnamed: RN13.3, RN14.6

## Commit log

2025-02-27 Changes for V3 hardware
    - Host adaptor base address can now be changed via DIP switch
    - Calculate parity bit and send to drive
    - Update I/O assignment

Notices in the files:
SCSIAdaptorXC9572-64 - Rev 02/SCSIAdaptor.kicad_pcb:
© Ken Lowe
